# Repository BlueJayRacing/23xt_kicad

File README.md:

# 23xt_kicad, JHU Blue Jay Racing Repository
This is the KiCad Repository for the JHU 23XT DAQ Sub-team.

## Installation and User Guide
GitHub & KiCad Guide: https://docs.google.com/document/d/1nFm-e38JEY4i58-0UFxqdLA5TKqWCrV3EDKR8jGpRfA/edit?usp=sharing 

As a summary, you should be using **KiCad Version 10.0**. All project will be modular, and you should be storing all your step files, symbols, & footprints within the created folders.

Schematic settings & layout settings are described in the guide, as well as component derating.

## Branch Guide
You should be working on a new branch for each revision of your board. It is only when your board gets ordered on JLC that it should be merged with the main branch.

<ins>Branch naming structure:</ins> [0X]-[boardname]_v[version]

Example:
> 01-main_board_v1

<ins>How-To Create a Branch:</ins>

```
git checkout -b [your_branch] main
git push -u origin [your_branch]
```

## KiCad Project Name

Create your KiCad project on YOUR branch, within your current project folder.

<ins>Project filepath:</ins> [your_folder]/[boardname]_v[X]

Example Path:
> 01-main_board/main_board_v1

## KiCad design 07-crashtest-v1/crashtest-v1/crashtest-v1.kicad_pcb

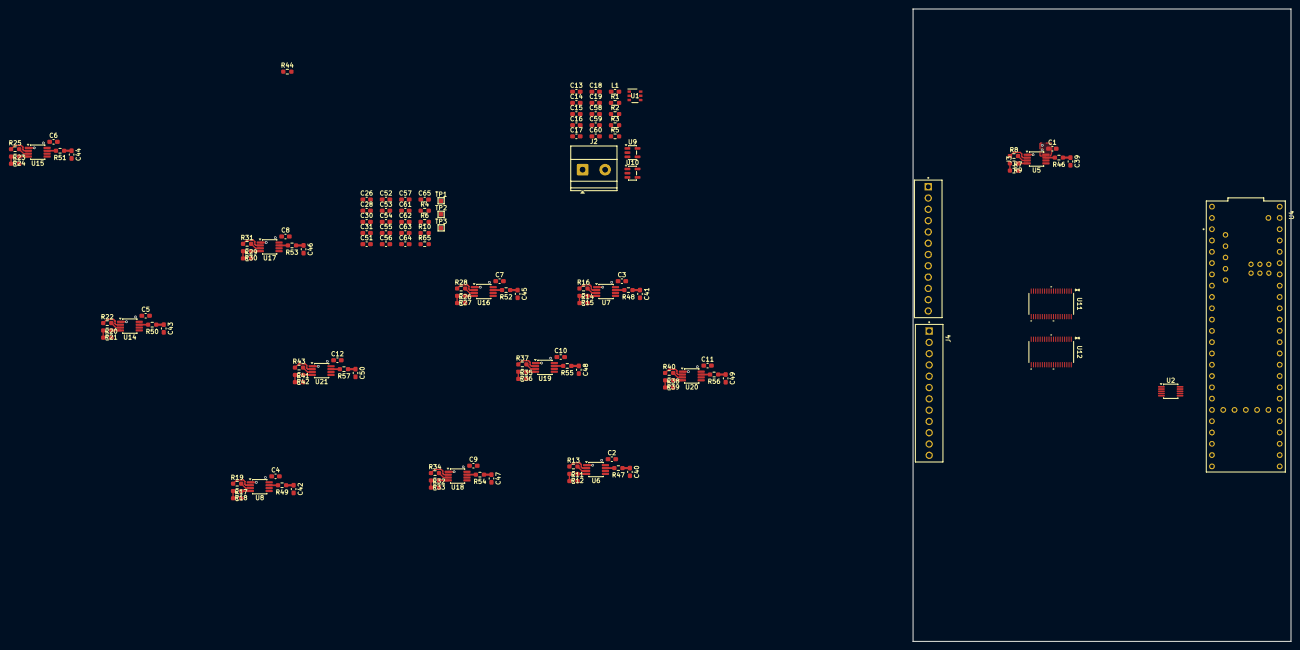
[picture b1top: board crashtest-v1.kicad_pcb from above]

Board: 4 copper layers, 85.0 x 142.2 mm, 133 parts (0 on the bottom side), 96 nets.

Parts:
C1, C2, C3, C4, C5, C6, C7, C8, C9, C10, C11, C12, C28: 0.1uF; C_0603_1608Metric_Pad1.08x0.95mm_HandSolder
C13, C54, C62: 10uF; C_0603_1608Metric_Pad1.08x0.95mm_HandSolder
C14, C15: 100nF; C_0603_1608Metric_Pad1.08x0.95mm_HandSolder
C16, C17, C53, C61: 22uF; C_0603_1608Metric_Pad1.08x0.95mm_HandSolder
C18, C19, C31, C51, C52, C55, C56, C57, C59, C60, C63, C64, C65: 1uF; C_0603_1608Metric_Pad1.08x0.95mm_HandSolder
C26: 220nF; C_0603_1608Metric_Pad1.08x0.95mm_HandSolder
C30: 1nF; C_0603_1608Metric_Pad1.08x0.95mm_HandSolder
C39, C40, C41, C42, C43, C44, C45, C46, C47, C48, C49, C50: 150nF; C_0603_1608Metric_Pad1.08x0.95mm_HandSolder
C58: 75pF; C_0603_1608Metric_Pad1.08x0.95mm_HandSolder
J2: Battery; TerminalBlock_Phoenix_MKDS-1,5-2-5.08_1x02_P5.08mm_Horizont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
J3, J4: Conn_01x12; PHOENIX_1725753
L1: 15uH; L_0603_1608Metric_Pad1.05x0.95mm_HandSolder
R1: 510k; R_0603_1608Metric_Pad0.98x0.95mm_HandSolder
R2: 49.9; R_0603_1608Metric_Pad0.98x0.95mm_HandSolder
R3: 95.3k; R_0603_1608Metric_Pad0.98x0.95mm_HandSolder
R4, R6, R7, R11, R14, R17, R20, R23, R26, R29, R32, R35, R38, R41: 350; R_0603_1608Metric_Pad0.98x0.95mm_HandSolder
R5: 13k; R_0603_1608Metric_Pad0.98x0.95mm_HandSolder
R8, R13, R16, R19, R22, R25, R28, R31, R34, R37, R40, R43: 845; R_0603_1608Metric_Pad0.98x0.95mm_HandSolder
R9, R10, R12, R15, R18, R21, R24, R27, R30, R33, R36, R39, R42, R46, R47, R48, R49, R50, R51, R52, R53, R54, R55, R56, R57: 1k; R_0603_1608Metric_Pad0.98x0.95mm_HandSolder
R44: 0; R_0603_1608Metric_Pad0.98x0.95mm_HandSolder
R65: 4.7k; R_0603_1608Metric_Pad0.98x0.95mm_HandSolder
TP1: MISO_adc; TestPoint_Pad_1.0x1.0mm
TP2: MOSI_adc; TestPoint_Pad_1.0x1.0mm
TP3: SCLK_adc; TestPoint_Pad_1.0x1.0mm
U1: TPS54202HDDCR; DDC0006A_L
U2: DAC60501ZDGSR; MSOP-10_3x3mm_P0.5mm
U4: DEV-16771; MODULE_DEV-16771
U5, U6, U7, U8, U14, U15, U16, U17, U18, U19, U20, U21: INA827AIDGKR; VSSOP-8_3x3mm_P0.65mm
U9: AP2112K-3.3; SOT-23-5
U10: AP2112K-2.5; SOT-23-5
U11, U12: ADS8688AIDBTR; DBT38_TEX-L

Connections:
2V5: C60.1, J3.1, J3.3, J3.5, J3.7, J3.9, J3.11, J4.1, J4.3, J4.5, J4.7, J4.9, J4.11, R4.1, U10.5 (VOUT)
2V5_EN: U4.15 (A1), U10.3 (EN)
3.3V: U4.3.3V_1 (3.3V), U4.3.3V_2 (3.3V), U4.3.3V_3 (3.3V)
3V3: C1.1, C2.1, C3.1, C4.1, C5.1, C6.1, C7.1, C8.1, C9.1, C10.1, C11.1, C12.1, C19.1, C28.1, C31.1, C56.1, C59.1, C64.1, U2.1 (VDD), U5.8 (VS+), U6.8 (VS+), U7.8 (VS+), U8.8 (VS+), U9.5 (VOUT), U10.1 (VIN), U11.34 (DVDD), U12.34 (DVDD), U14.8 (VS+), U15.8 (VS+), U16.8 (VS+), U17.8 (VS+), U18.8 (VS+), U19.8 (VS+), U20.8 (VS+), U21.8 (VS+)
3V3_EN: U4.14 (A0), U9.3 (EN)
5V: C16.1, C17.1, C18.1, C51.2, C55.1, C57.2, C65.1, L1.2, R2.1, R44.1, U9.1 (VIN), U11.9 (AVDD), U11.30 (AVDD), U12.9 (AVDD), U12.30 (AVDD)
/Analog/AIN0: C39.2, R46.2, U11.16 (AIN_0P)
/Analog/AIN1: C40.2, R47.2, U11.18 (AIN_1P)
/Analog/AIN2: C41.2, R48.2, U11.21 (AIN_2P)
/Analog/AIN3: C42.2, R49.2, U11.23 (AIN_3P)
/Analog/AIN4: C43.2, R50.2, U11.25 (AIN_4P)
/Analog/AIN5: C44.2, R51.2, U11.27 (AIN_5P)
/Analog/AIN6: C45.2, R52.2, U12.16 (AIN_0P)
/Analog/AIN7: C46.2, R53.2, U12.18 (AIN_1P)
/Analog/AIN8: C47.2, R54.2, U12.21 (AIN_2P)
/Analog/AIN9: C48.2, R55.2, U12.23 (AIN_3P)
/Analog/AIN10: C49.2, R56.2, U12.25 (AIN_4P)
/Analog/AIN11: C50.2, R57.2, U12.27 (AIN_5P)
/Analog/REFCAP1: C52.1, C53.1, U11.7 (REFCAP)
/Analog/REFCAP2: C61.1, C63.1, U12.7 (REFCAP)
/Analog/REFIO1: C54.1, U11.5 (REFIO)
/Analog/REFIO2: C62.1, U12.5 (REFIO)
ADC1_ALARM: U4.17 (A3), U11.35 (ALARM)
ADC1_NRST: U4.16 (A2), U11.2 (*RST/*PD)
ADC2_ALARM: U4.19 (A5), U12.35 (ALARM)
ADC2_NRST: U4.18 (A4), U12.2 (*RST/*PD)
ADC_CS: U4.10 (CS1), U11.38 (*CS), U12.38 (*CS)
ADC_MISO: TP1.1 (1_1), U4.12 (MISO), U12.36 (SDO)
ADC_MOSI: TP2.1 (1_1), U4.11 (MOSI), U11.1 (SDI), U12.1 (SDI)
ADC_SCLK: TP3.1 (1_1), U4.13 (SCK), U11.37 (SCLK), U12.37 (SCLK)
BREF_F: R10.2, U5.1 (IN-), U6.1 (IN-), U7.1 (IN-), U8.1 (IN-), U14.1 (IN-), U15.1 (IN-), U16.1 (IN-), U17.1 (IN-), U18.1 (IN-), U19.1 (IN-), U20.1 (IN-), U21.1 (IN-)
CS_DAC: U2.7 (*SYNC/A0), U4.25 (A11)
GND: C1.2, C2.2, C3.2, C4.2, C5.2, C6.2, C7.2, C8.2, C9.2, C10.2, C11.2, C12.2, C13.2, C14.2, C16.2, C17.2, C18.2, C19.2, C26.1, C28.2, C30.1, C31.2, C39.1, C40.1, C41.1, C42.1, C43.1, C44.1, C45.1, C46.1, C47.1, C48.1, C49.1, C50.1, C51.1, C52.2, C53.2, C54.2, C55.2, C56.2, C57.1, C59.2, C60.2, C61.2, C62.2, C63.2, C64.2, C65.2, J2.1, R5.2, R6.2, R7.2, R11.2, R14.2, R17.2, R20.2, R23.2, R26.2, R29.2, R32.2, R35.2, R38.2, R41.2, R65.2, U1.1 (GND), U2.4 (AGND), U4.GND1 (GND), U4.GND2 (GND), U4.GND3 (GND), U4.GND4 (GND), U4.GND5 (GND), U4.USB_GND1 (USB_GND), U4.USB_GND2 (USB_GND), U5.5 (VS-), U6.5 (VS-), U7.5 (VS-), U8.5 (VS-), U9.2 (GND), U10.2 (GND), U11.3 (DAISY), U11.4 (*REFSEL), U11.6 (REFGND), U11.8 (AGND), U11.10 (AUX_IN), U11.11 (AUX_GND), U11.12 (AIN_6P), U11.13 (AIN_6GND), U11.14 (AIN_7P), U11.15 (AIN_7GND), U11.17 (AIN_0GND), U11.19 (AIN_1GND), U11.20 (AIN_2GND), U11.22 (AIN_3GND), U11.24 (AIN_4GND), U11.26 (AIN_5GND), U11.28 (AGND), U11.29 (AGND), U11.31 (AGND), U11.32 (AGND), U11.33 (DGND), U12.4 (*REFSEL), U12.6 (REFGND), U12.8 (AGND), U12.10 (AUX_IN), U12.11 (AUX_GND), U12.12 (AIN_6P), U12.13 (AIN_6GND), U12.14 (AIN_7P), U12.15 (AIN_7GND), U12.17 (AIN_0GND), U12.19 (AIN_1GND), U12.20 (AIN_2GND), U12.22 (AIN_3GND), U12.24 (AIN_4GND), U12.26 (AIN_5GND), U12.28 (AGND), U12.29 (AGND), U12.31 (AGND), U12.32 (AGND), U12.33 (DGND), U14.5 (VS-), U15.5 (VS-), U16.5 (VS-), U17.5 (VS-), U18.5 (VS-), U19.5 (VS-), U20.5 (VS-), U21.5 (VS-)
MOSI_DAC: U2.8 (SDIN/SDA), U4.26 (A12)
unnamed: C58.1, R2.2, R3.1
unnamed: R8.1, U5.3 (RG)
unnamed: R8.2, U5.2 (RG)
unnamed: R4.2, R6.1, R10.1
unnamed: R13.1, U6.3 (RG)
unnamed: R13.2, U6.2 (RG)
unnamed: R16.1, U7.3 (RG)
unnamed: R16.2, U7.2 (RG)
unnamed: R19.1, U8.3 (RG)
unnamed: R19.2, U8.2 (RG)
unnamed: R22.1, U14.3 (RG)
unnamed: R22.2, U14.2 (RG)
unnamed: R25.1, U15.3 (RG)
unnamed: R25.2, U15.2 (RG)
unnamed: R28.1, U16.3 (RG)
unnamed: R28.2, U16.2 (RG)
unnamed: R31.1, U17.3 (RG)
unnamed: R31.2, U17.2 (RG)
unnamed: R34.1, U18.3 (RG)
unnamed: R34.2, U18.2 (RG)
unnamed: R37.1, U19.3 (RG)
unnamed: R37.2, U19.2 (RG)
unnamed: R40.1, U20.3 (RG)
unnamed: R40.2, U20.2 (RG)
unnamed: R43.1, U21.3 (RG)
unnamed: R43.2, U21.2 (RG)
unnamed: R44.2, U4.VIN
unnamed: C15.1, U1.6 (BOOT)
unnamed: R1.2, U1.5 (EN)
unnamed: C58.2, R3.2, R5.1, U1.4 (FB)
unnamed: C15.2, L1.1, U1.2 (SW)
unnamed: R65.1, U2.5 (SPI2C)
unnamed: R9.2, U5.4 (IN+)
unnamed: R46.1, U5.7 (VOUT)
unnamed: R12.2, U6.4 (IN+)
unnamed: R47.1, U6.7 (VOUT)
unnamed: R15.2, U7.4 (IN+)
unnamed: R48.1, U7.7 (VOUT)
unnamed: R18.2, U8.4 (IN+)
unnamed: R49.1, U8.7 (VOUT)
unnamed: U11.36 (SDO), U12.3 (DAISY)
unnamed: R21.2, U14.4 (IN+)
unnamed: R50.1, U14.7 (VOUT)
unnamed: R24.2, U15.4 (IN+)
unnamed: R51.1, U15.7 (VOUT)
unnamed: R27.2, U16.4 (IN+)
unnamed: R52.1, U16.7 (VOUT)
unnamed: R30.2, U17.4 (IN+)
unnamed: R53.1, U17.7 (VOUT)
unnamed: R33.2, U18.4 (IN+)
unnamed: R54.1, U18.7 (VOUT)
unnamed: R36.2, U19.4 (IN+)
unnamed: R55.1, U19.7 (VOUT)
unnamed: R39.2, U20.4 (IN+)
unnamed: R56.1, U20.7 (VOUT)
unnamed: R42.2, U21.4 (IN+)
unnamed: R57.1, U21.7 (VOUT)
SCLK_DAC: U2.6 (SCLK/SCL), U4.27 (A13)
SIG0: J3.2, R7.1, R9.1, R11.1, R12.1, R14.1, R15.1, R17.1, R18.1, R20.1, R21.1, R23.1, R24.1, R26.1, R27.1, R29.1, R30.1, R32.1, R33.1, R35.1, R36.1, R38.1, R39.1, R41.1, R42.1
VBAT: C13.1, C14.1, J2.2, R1.1, U1.3 (VIN)
VREFIO_C: C26.2, U2.10 (VREFIO)
VREF_1V65: C30.2, U2.2 (VOUT), U5.6 (REF), U6.6 (REF), U7.6 (REF), U8.6 (REF), U14.6 (REF), U15.6 (REF), U16.6 (REF), U17.6 (REF), U18.6 (REF), U19.6 (REF), U20.6 (REF), U21.6 (REF)

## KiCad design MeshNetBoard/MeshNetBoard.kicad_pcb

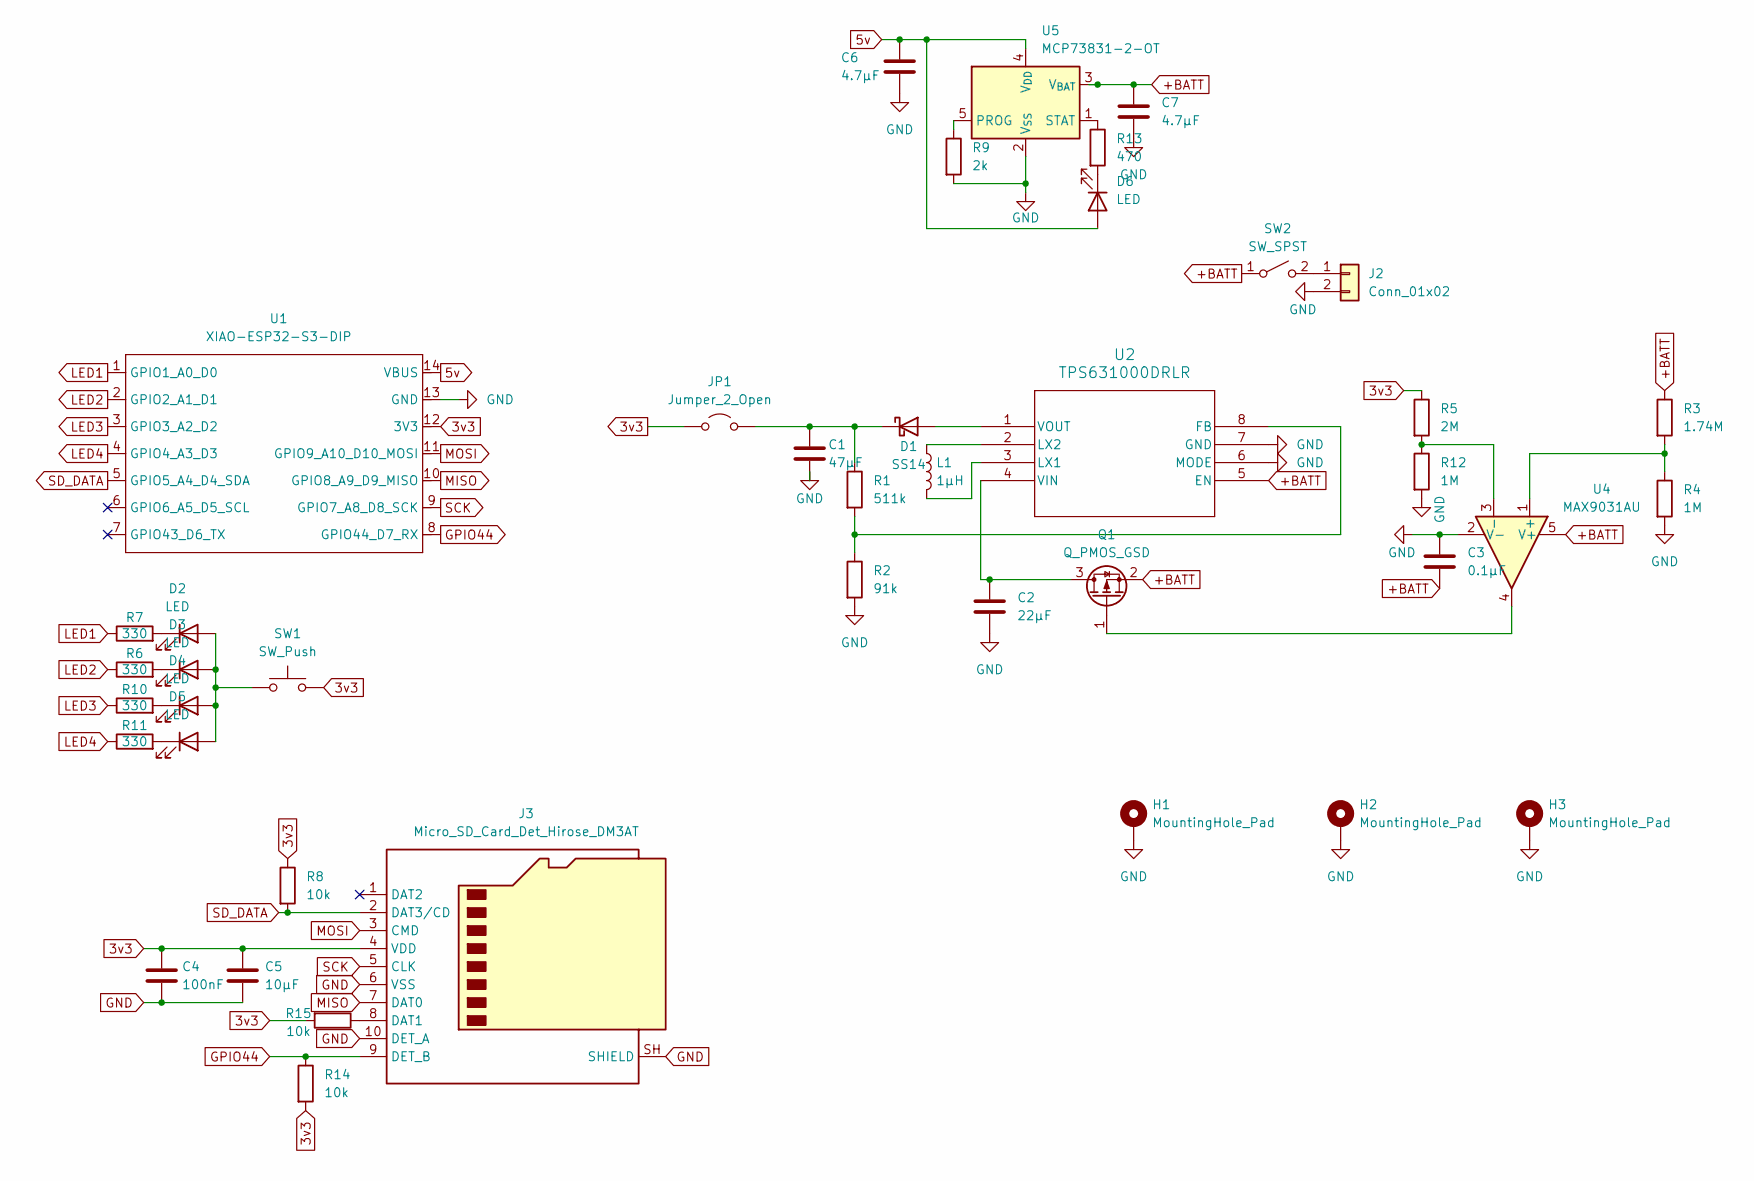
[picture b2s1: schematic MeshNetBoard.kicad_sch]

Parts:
C1: 47µF; C_0603_1608Metric_Pad1.08x0.95mm_HandSolder
C2: 22µF; C_0603_1608Metric_Pad1.08x0.95mm_HandSolder
C3: 0.1μF; C_0603_1608Metric_Pad1.08x0.95mm_HandSolder
C4: 100nF; C_0603_1608Metric_Pad1.08x0.95mm_HandSolder
C5: 10µF; C_0603_1608Metric_Pad1.08x0.95mm_HandSolder
C6, C7: 4.7µF; C_0603_1608Metric_Pad1.08x0.95mm_HandSolder
D1: SS14; D_SMA
D2, D3, D4, D5, D6: LED; LED_1206_3216Metric_Pad1.42x1.75mm_HandSolder
H1, H2, H3: MountingHole_Pad; MountingHole_2.2mm_M2_Pad_TopBottom
J2: Conn_01x02; JST_PH_S2B-PH-K_1x02_P2.00mm_Horizontal
J3: Micro_SD_Card_Det_Hirose_DM3AT; microSD_HC_Hirose_DM3AT-SF-PEJM5
JP1: Jumper_2_Open; PinSocket_1x02_P2.54mm_Vertical
L1: 1µH; L_0603_1608Metric_Pad1.05x0.95mm_HandSolder
Q1: Q_PMOS_GSD; SOT-23
R1: 511k; R_0603_1608Metric_Pad0.98x0.95mm_HandSolder
R2: 91k; R_0603_1608Metric_Pad0.98x0.95mm_HandSolder
R3: 1.74M; R_0603_1608Metric_Pad0.98x0.95mm_HandSolder
R4, R12: 1M; R_0603_1608Metric_Pad0.98x0.95mm_HandSolder
R5: 2M; R_0603_1608Metric_Pad0.98x0.95mm_HandSolder
R6, R7, R10, R11: 330; R_0603_1608Metric_Pad0.98x0.95mm_HandSolder
R8, R14, R15: 10k; R_0603_1608Metric_Pad0.98x0.95mm_HandSolder
R9: 2k; R_0603_1608Metric_Pad0.98x0.95mm_HandSolder
R13: 470; R_0603_1608Metric_Pad0.98x0.95mm_HandSolder
SW1: SW_Push; SW_PUSH_6mm_H5mm
SW2: SW_SPST; SW_Slide_SPDT_Angled_CK_OS102011MA1Q
U1: XIAO-ESP32-S3-DIP
U2: TPS631000DRLR; TPS631000DRLR_TEX
U4: MAX9031AU; SOT-23-5
U5: MCP73831-2-OT; SOT-23-5

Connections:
3v3: C4.1, C5.1, J3.4 (VDD), JP1.1 (A), R5.1, R8.1, R14.2, R15.2, SW1.2, U1.12 (3V3)
5v: C6.1, D6.2 (A), U1.14 (VBUS), U5.4 (V_{DD})
+BATT: C3.2, C7.1, Q1.2 (S), R3.1, SW2.1 (A), U2.5 (EN), U4.5 (V+), U5.3 (V_{BAT})
GND: C1.2, C2.2, C3.1, C4.2, C5.2, C6.2, C7.2, H1.1 (1_1), H2.1 (1_1), H3.1 (1_1), J2.2, J3.6 (VSS), J3.10 (DET_A), J3.SH (SHIELD), R2.2, R4.2, R9.2, R12.2, U1.13 (GND), U2.6 (MODE), U2.7 (GND), U4.2 (V-), U5.2 (V_{SS})
GPIO44: J3.9 (DET_B), R14.1, U1.8 (GPIO44_D7_RX)
LED1: R7.1, U1.1 (GPIO1_A0_D0)
LED2: R6.1, U1.2 (GPIO2_A1_D1)
LED3: R10.1, U1.3 (GPIO3_A2_D2)
LED4: R11.1, U1.4 (GPIO4_A3_D3)
MISO: J3.7 (DAT0), U1.10 (GPIO8_A9_D9_MISO)
MOSI: J3.3 (CMD), U1.11 (GPIO9_A10_D10_MOSI)
unnamed: D1.2 (A), U2.1 (VOUT)
unnamed: C1.1, D1.1 (K), JP1.2 (B), R1.1
unnamed: D2.2 (A), D3.2 (A), D4.2 (A), D5.2 (A), SW1.1
unnamed: D2.1 (K), R7.2
unnamed: D3.1 (K), R6.2
unnamed: D4.1 (K), R10.2
unnamed: D5.1 (K), R11.2
unnamed: D6.1 (K), R13.2
unnamed: J2.1, SW2.2 (B)
unnamed: J3.8 (DAT1), R15.1
unnamed: C2.1, Q1.3 (D), U2.4 (VIN)
unnamed: Q1.1 (G), U4.4
unnamed: R1.2, R2.1, U2.8 (FB)
unnamed: L1.2, U2.3 (LX1)
unnamed: L1.1, U2.2 (LX2)
unnamed: R3.2, R4.1, U4.1 (+)
unnamed: R5.2, R12.1, U4.3 (-)
unnamed: R9.1, U5.5 (PROG)
unnamed: R13.1, U5.1 (STAT)
SCK: J3.5 (CLK), U1.9 (GPIO7_A8_D8_SCK)
SD_DATA: J3.2 (DAT3/CD), R8.2, U1.5 (GPIO5_A4_D4_SDA)

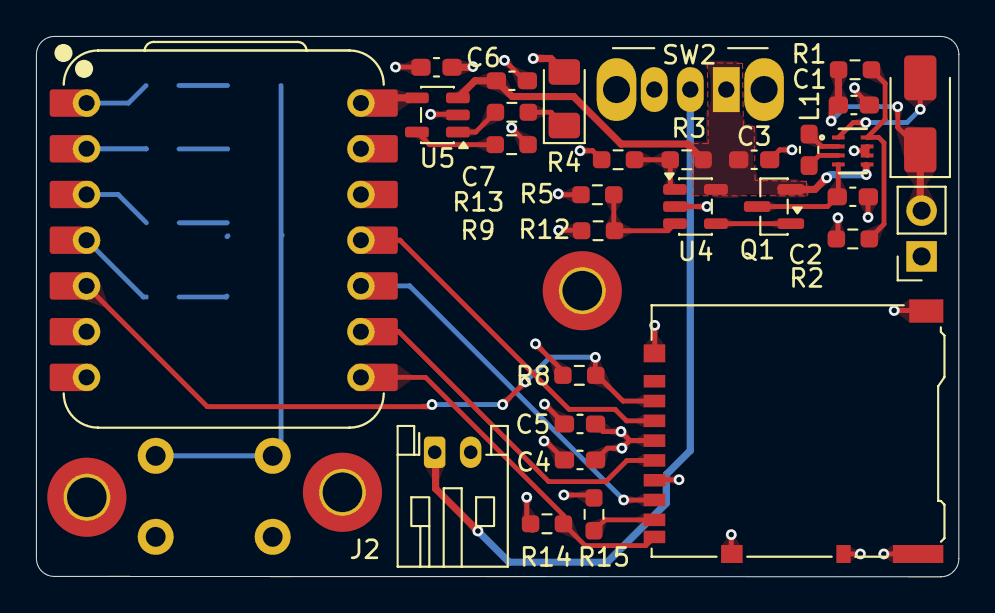
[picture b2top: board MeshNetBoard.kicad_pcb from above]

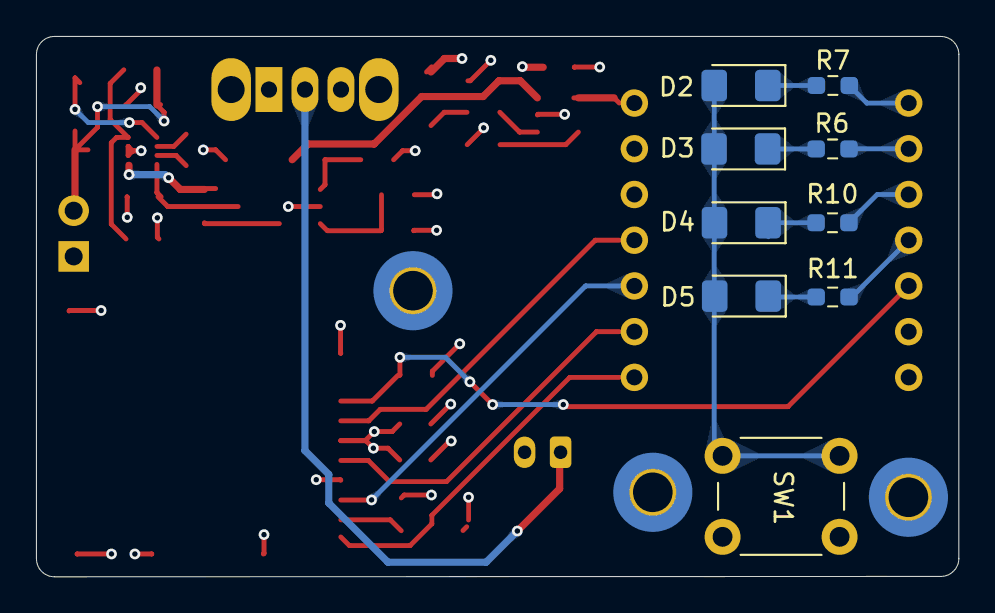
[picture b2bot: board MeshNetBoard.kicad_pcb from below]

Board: 4 copper layers, 51.2 x 30.0 mm, 42 parts (9 on the bottom side), 32 nets.

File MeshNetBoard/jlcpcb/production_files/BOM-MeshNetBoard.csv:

Comment,Designator,Footprint,LCSC,Quantity
0.1μF,C3,C_0603_1608Metric_Pad1.08x0.95mm_HandSolder,C125205,1
1.74M,R3,R_0603_1608Metric_Pad0.98x0.95mm_HandSolder,C422975,1
100nF,C4,C_0603_1608Metric_Pad1.08x0.95mm_HandSolder,C14663,1
10k,"R14,R15,R8",R_0603_1608Metric_Pad0.98x0.95mm_HandSolder,C23192,3
10µF,C5,C_0603_1608Metric_Pad1.08x0.95mm_HandSolder,C19702,1
1M,"R12,R4",R_0603_1608Metric_Pad0.98x0.95mm_HandSolder,C22935,2
1µH,L1,L_0603_1608Metric_Pad1.05x0.95mm_HandSolder,C98326,1
22µF,C2,C_0603_1608Metric_Pad1.08x0.95mm_HandSolder,C59461,1
2M,R5,R_0603_1608Metric_Pad0.98x0.95mm_HandSolder,C22976,1
2k,R9,R_0603_1608Metric_Pad0.98x0.95mm_HandSolder,C22975,1
330,"R10,R11,R6,R7",R_0603_1608Metric_Pad0.98x0.95mm_HandSolder,C23138,4
4.7µF,"C6,C7",C_0603_1608Metric_Pad1.08x0.95mm_HandSolder,C19666,2
470,R13,R_0603_1608Metric_Pad0.98x0.95mm_HandSolder,C23179,1
47µF,C1,C_0603_1608Metric_Pad1.08x0.95mm_HandSolder,C140782,1
511k,R1,R_0603_1608Metric_Pad0.98x0.95mm_HandSolder,C23194,1
91k,R2,R_0603_1608Metric_Pad0.98x0.95mm_HandSolder,C23265,1
Conn_01x02,J2,JST_PH_S2B-PH-K_1x02_P2.00mm_Horizontal,C173752,1
Jumper_2_Open,JP1,PinSocket_1x02_P2.54mm_Vertical,C6823945,1
LED,"D2,D3,D4,D5,D6",LED_1206_3216Metric_Pad1.42x1.75mm_HandSolder,C2827254,5
MAX9031AU,U4,SOT-23-5,C117531,1
MCP73831-2-OT,U5,SOT-23-5,C424093,1
Micro_SD_Card_Det_Hirose_DM3AT,J3,microSD_HC_Hirose_DM3AT-SF-PEJM5,C114218,1
Q_PMOS_GSD,Q1,SOT-23,C10487,1
SS14,D1,D_SMA,C2480,1
SW_Push,SW1,SW_PUSH_6mm_H5mm,C428628,1
SW_SPST,SW2,SW_Slide_SPDT_Angled_CK_OS102011MA1Q,C19192981,1
TPS631000DRLR,U2,TPS631000DRLR_TEX,C5219190,1
XIAO-ESP32-S3-DIP,U1,XIAO-ESP32-S3-DIP,C48405120,1

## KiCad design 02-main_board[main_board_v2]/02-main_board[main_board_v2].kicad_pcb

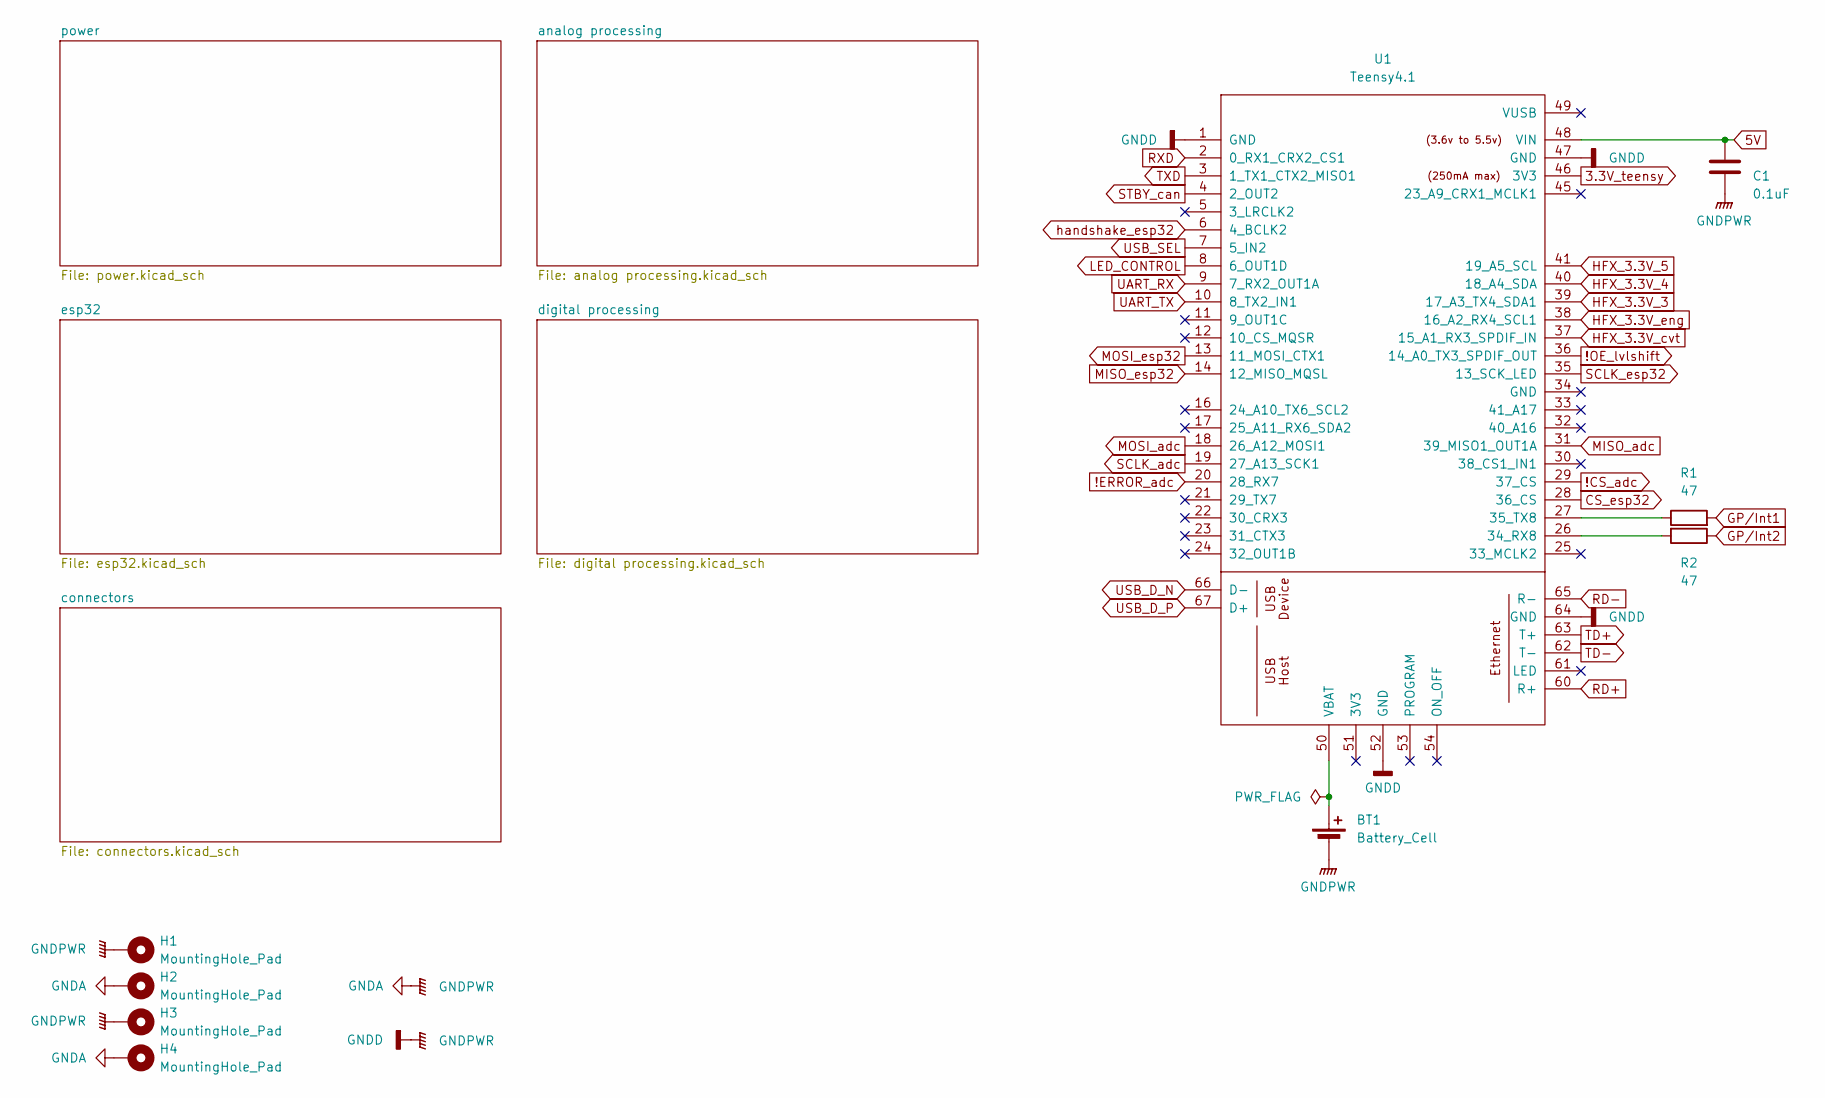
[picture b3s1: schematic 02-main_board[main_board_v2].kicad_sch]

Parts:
BT1: Battery_Cell; BatteryHolder_LINX_BAT-HLD-012-SMT
C1: 0.1uF; C_0603_1608Metric; MPN CC0603KRX7R9BB104; LCSC C14663
H1, H2, H3, H4: MountingHole_Pad; MountingHole_2.5mm_Pad
R1, R2: 47; R_0603_1608Metric; MPN RC0603JR-0747RL; LCSC C23182
U1: Teensy4.1; Teensy41_OG

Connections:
3.3V_teensy: U1.46 (3V3); also elsewhere on the board
5V: C1.2, U1.48 (VIN); also elsewhere on the board
!CS_adc: U1.29 (37_CS); also elsewhere on the board
!ERROR_adc: U1.20 (28_RX7); also elsewhere on the board
!OE_lvlshift: U1.36 (14_A0_TX3_SPDIF_OUT); also elsewhere on the board
CS_esp32: U1.28 (36_CS); also elsewhere on the board
GNDA: BT1.2 (-), C1.1, H1.1 (1_1), H2.1 (1_1), H3.1 (1_1), H4.1 (1_1), U1.1 (GND), U1.47 (GND), U1.52 (GND), U1.64 (GND); also elsewhere on the board
GP/Int1: R1.2; also elsewhere on the board
GP/Int2: R2.1; also elsewhere on the board
HFX_3.3V_3: U1.39 (17_A3_TX4_SDA1); also elsewhere on the board
HFX_3.3V_4: U1.40 (18_A4_SDA); also elsewhere on the board
HFX_3.3V_5: U1.41 (19_A5_SCL); also elsewhere on the board
HFX_3.3V_cvt: U1.37 (15_A1_RX3_SPDIF_IN); also elsewhere on the board
HFX_3.3V_eng: U1.38 (16_A2_RX4_SCL1); also elsewhere on the board
LED_CONTROL: U1.8 (6_OUT1D); also elsewhere on the board
MISO_adc: U1.31 (39_MISO1_OUT1A); also elsewhere on the board
MISO_esp32: U1.14 (12_MISO_MQSL); also elsewhere on the board
MOSI_adc: U1.18 (26_A12_MOSI1); also elsewhere on the board
MOSI_esp32: U1.13 (11_MOSI_CTX1); also elsewhere on the board
unnamed: BT1.1 (+), U1.50 (VBAT)
unnamed: R2.2, U1.26 (34_RX8)
unnamed: R1.1, U1.27 (35_TX8)
RD+: U1.60 (R+); also elsewhere on the board
RD-: U1.65 (R-); also elsewhere on the board
RXD: U1.2 (0_RX1_CRX2_CS1); also elsewhere on the board
SCLK_adc: U1.19 (27_A13_SCK1); also elsewhere on the board
SCLK_esp32: U1.35 (13_SCK_LED); also elsewhere on the board
STBY_can: U1.4 (2_OUT2); also elsewhere on the board
TD+: U1.63 (T+); also elsewhere on the board
TD-: U1.62 (T-); also elsewhere on the board
TXD: U1.3 (1_TX1_CTX2_MISO1); also elsewhere on the board
UART_RX: U1.9 (7_RX2_OUT1A); also elsewhere on the board
UART_TX: U1.10 (8_TX2_IN1); also elsewhere on the board
USB_D_N: U1.66 (D-); also elsewhere on the board
USB_D_P: U1.67 (D+); also elsewhere on the board
USB_SEL: U1.7 (5_IN2); also elsewhere on the board
handshake_esp32: U1.6 (4_BCLK2); also elsewhere on the board

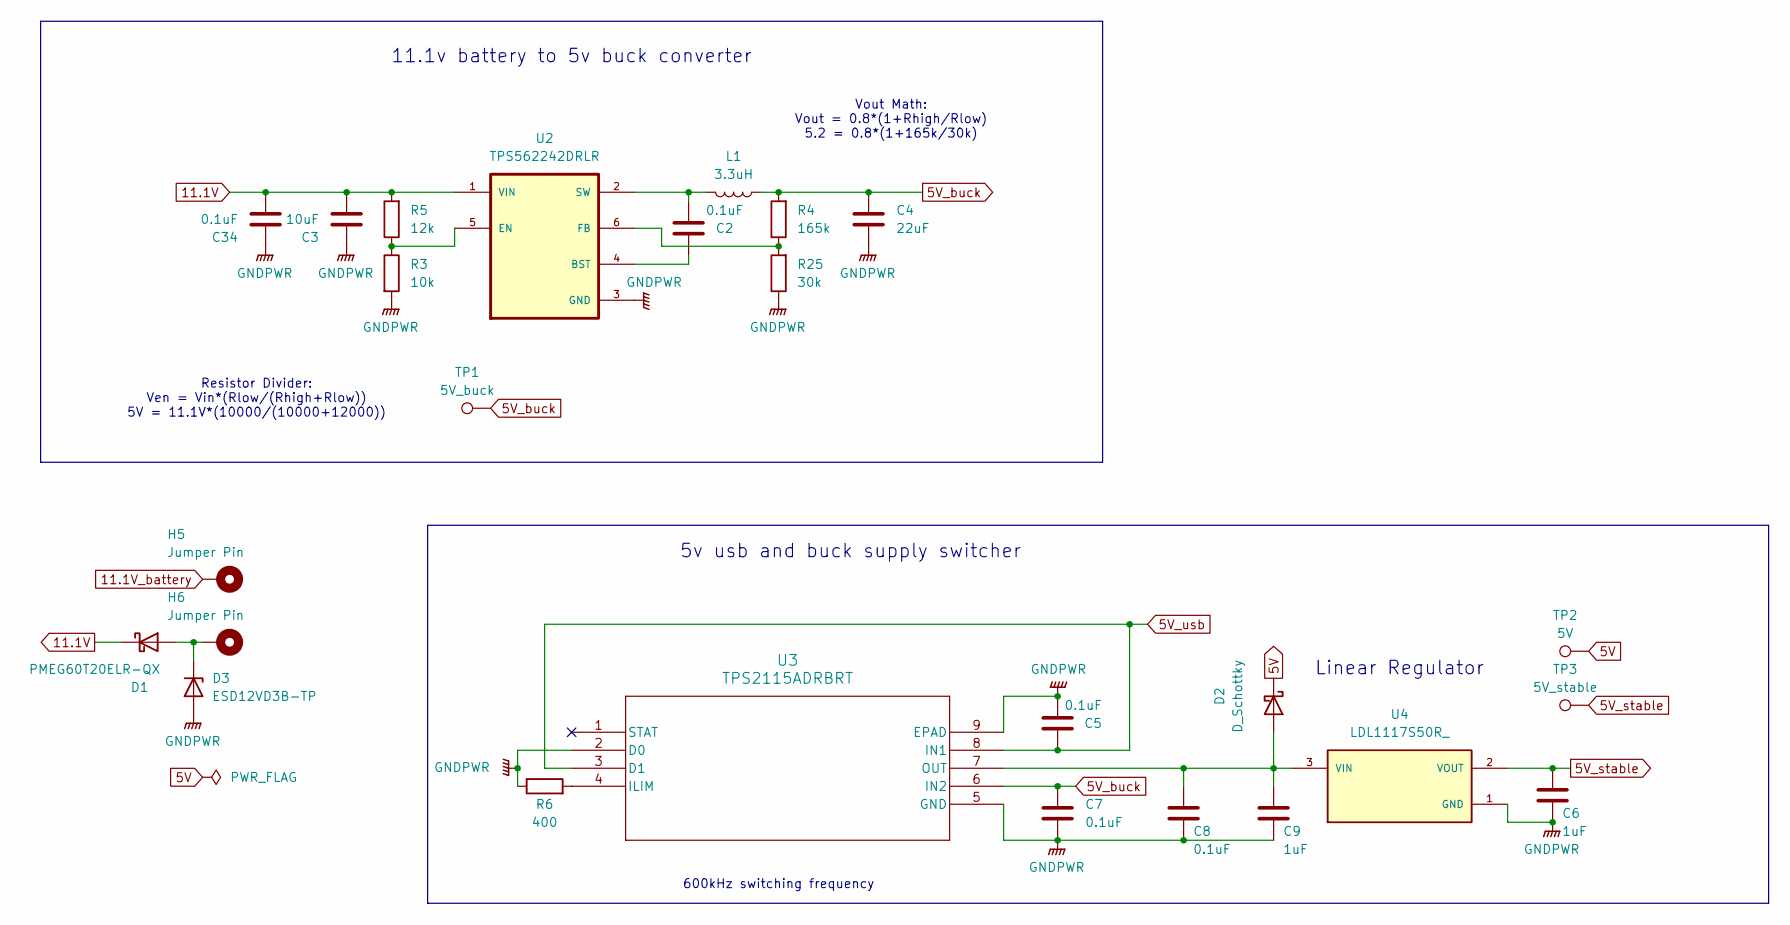
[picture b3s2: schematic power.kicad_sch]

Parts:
C2: 0.1uF; C_0603_1608Metric; MPN CL10B474KO8NNND; LCSC C14663
C3: 10uF; C_0603_1608Metric; MPN GMC10X5R106M16NT; LCSC C96446
C4: 22uF; C_0603_1608Metric; MPN GRM188R61A226ME15D; LCSC C59461
C5, C7, C8: 0.1uF; C_0603_1608Metric; MPN CC0603KRX7R9BB104; LCSC C14663
C6, C9: 1uF; C_0603_1608Metric; MPN CL10A105KA8NFNC; LCSC C15849
C34: 0.1uF; C_0603_1608Metric; MPN CL10A475KO8NNNC; LCSC C14663
D1: PMEG60T20ELR-QX; Nexperia_CFP3_SOD-123W
D2: D_Schottky; Nexperia_CFP3_SOD-123W
D3: ESD12VD3B-TP; D_SOD-323
H5, H6: Jumper Pin; PinHeader_1x01_P2.54mm_Vertical
L1: 3.3uH; IND_TAIYO_NRS4018_TAY; MPN NRS4018T3R3MDGJ
R3: 10k; R_0603_1608Metric; MPN CRCW060310K0FKEA; LCSC C25804
R4: 165k; R_0603_1608Metric; MPN RNCF0603DTE165K
R5: 12k; R_0603_1608Metric; MPN CRCW060312K0FKEA; LCSC C22790
R6: 400; R_0603_1608Metric; MPN RK73H1JTTD4020F
R25: 30k; R_0603_1608Metric; MPN TFAS0603R3002F-T5
TP1: 5V_buck; TestPoint_Pad_1.0x1.0mm
TP2: 5V; TestPoint_Pad_1.0x1.0mm
TP3: 5V_stable; TestPoint_Pad_1.0x1.0mm
U2: TPS562242DRLR; SOT50P160X60-6N; PARTREV A
U3: TPS2115ADRBRT; SON65P300X300X100-9N-D; MPN TPS2115ADRBR
U4: LDL1117S50R_; PARTREV 7

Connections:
5V: D2.1 (K), TP2.1 (1_1); also elsewhere on the board
5V_buck: C4.1, C7.1, L1.1, R4.2, TP1.1 (1_1), U3.6 (IN2)
5V_stable: C6.1, TP3.1 (1_1), U4.2 (VOUT), U4.4 (VOUT); also elsewhere on the board
5V_usb: C5.1, U3.3 (D1), U3.8 (IN1); also elsewhere on the board
11.1V: C3.2, C34.2, D1.1 (K), R5.2, U2.1 (VIN); also elsewhere on the board
11.1V_battery: H5.1 (1_1); also elsewhere on the board
GNDA: C3.1, C4.2, C5.2, C6.2, C7.2, C8.2, C9.2, C34.1, D3.2 (A), R3.2, R6.1, R25.1, U2.3 (GND), U3.2 (D0), U3.5 (GND), U3.9 (EPAD), U4.1 (GND); also elsewhere on the board
unnamed: D1.2 (A), D3.1 (K), H6.1 (1_1)
unnamed: C8.1, C9.1, D2.2 (A), U3.7 (OUT), U4.3 (VIN)
unnamed: C2.1, U2.4 (BST)
unnamed: R3.1, R5.1, U2.5 (EN)
unnamed: R4.1, R25.2, U2.6 (FB)
unnamed: C2.2, L1.2, U2.2 (SW)
unnamed: R6.2, U3.4 (ILIM)

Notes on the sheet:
Resistor Divider: Ven = Vin*(Rlow/(Rhigh+Rlow)) 5V = 11.1V*(10000/(10000+12000))
Vout Math: Vout = 0.8*(1+Rhigh/Rlow) 5.2 = 0.8*(1+165k/30k)
5v usb and buck supply switcher
Linear Regulator
600kHz switching frequency
11.1v battery to 5v buck converter

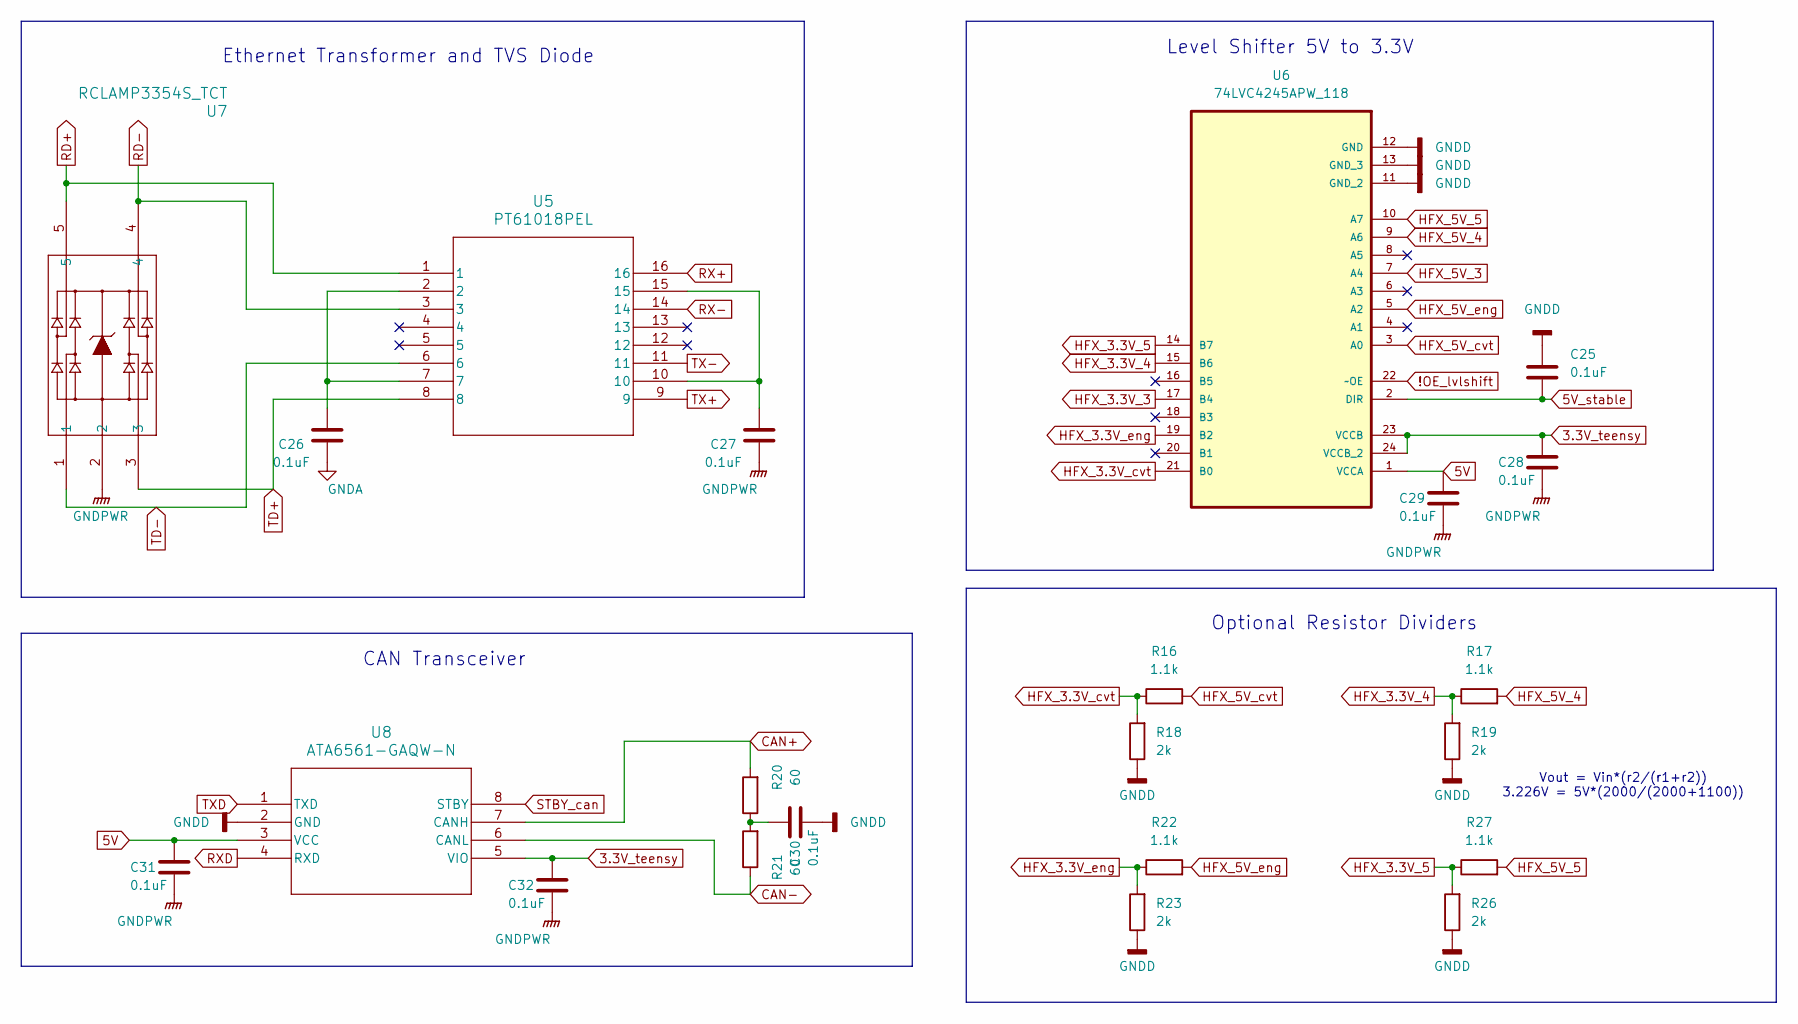
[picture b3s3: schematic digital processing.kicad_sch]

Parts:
C25, C26, C27, C28, C29, C30, C31, C32: 0.1uF; C_0603_1608Metric; MPN CC0603KRX7R9BB104; LCSC C14663
R16, R17, R22, R27: 1.1k; R_0603_1608Metric; MPN RT0603BRD071K1L
R18, R19, R23, R26: 2k; R_0603_1608Metric; MPN RC0603FR-072KL
R20, R21: 60; R_0603_1608Metric; MPN CRCW060360R4FKEA
U5: PT61018PEL; SOIC_PT61018PEL
U6: 74LVC4245APW_118
U7: RCLAMP3354S_TCT
U8: ATA6561-GAQW-N

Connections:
3.3V_teensy: C28.2, C32.2, U6.23 (VCCB), U6.24 (VCCB_2), U8.5 (VIO); also elsewhere on the board
5V: C29.2, C31.2, U6.1 (VCCA), U8.3 (VCC); also elsewhere on the board
5V_stable: C25.1, U6.2 (DIR); also elsewhere on the board
!OE_lvlshift: U6.22 (~OE); also elsewhere on the board
CAN+: R20.2, U8.7 (CANH); also elsewhere on the board
CAN-: R21.1, U8.6 (CANL); also elsewhere on the board
GNDA: C25.2, C26.2, C27.2, C28.1, C29.1, C30.1, C31.1, C32.1, R18.1, R19.1, R23.1, R26.1, U6.11 (GND_2), U6.12 (GND), U6.13 (GND_3), U7.2, U8.2 (GND); also elsewhere on the board
HFX_3.3V_3: U6.17 (B4); also elsewhere on the board
HFX_3.3V_4: R17.1, R19.2, U6.15 (B6); also elsewhere on the board
HFX_3.3V_5: R26.2, R27.1, U6.14 (B7); also elsewhere on the board
HFX_3.3V_cvt: R16.1, R18.2, U6.21 (B0); also elsewhere on the board
HFX_3.3V_eng: R22.1, R23.2, U6.19 (B2); also elsewhere on the board
HFX_5V_3: U6.7 (A4); also elsewhere on the board
HFX_5V_4: R17.2, U6.9 (A6); also elsewhere on the board
HFX_5V_5: R27.2, U6.10 (A7); also elsewhere on the board
HFX_5V_cvt: R16.2, U6.3 (A0); also elsewhere on the board
HFX_5V_eng: R22.2, U6.5 (A2); also elsewhere on the board
unnamed: C26.1, U5.2, U5.7
unnamed: C27.1, U5.10, U5.15
unnamed: C30.2, R20.1, R21.2
RD+: U5.1, U7.5; also elsewhere on the board
RD-: U5.3, U7.4; also elsewhere on the board
RX+: U5.16; also elsewhere on the board
RX-: U5.14; also elsewhere on the board
RXD: U8.4 (RXD); also elsewhere on the board
STBY_can: U8.8 (STBY); also elsewhere on the board
TD+: U5.8, U7.3; also elsewhere on the board
TD-: U5.6, U7.1; also elsewhere on the board
TX+: U5.9; also elsewhere on the board
TX-: U5.11; also elsewhere on the board
TXD: U8.1 (TXD); also elsewhere on the board

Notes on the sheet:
Optional Resistor Dividers
Vout = Vin*(r2/(r1+r2)) 3.226V = 5V*(2000/(2000+1100))
Level Shifter 5V to 3.3V
Ethernet Transformer and TVS Diode
CAN Transceiver
